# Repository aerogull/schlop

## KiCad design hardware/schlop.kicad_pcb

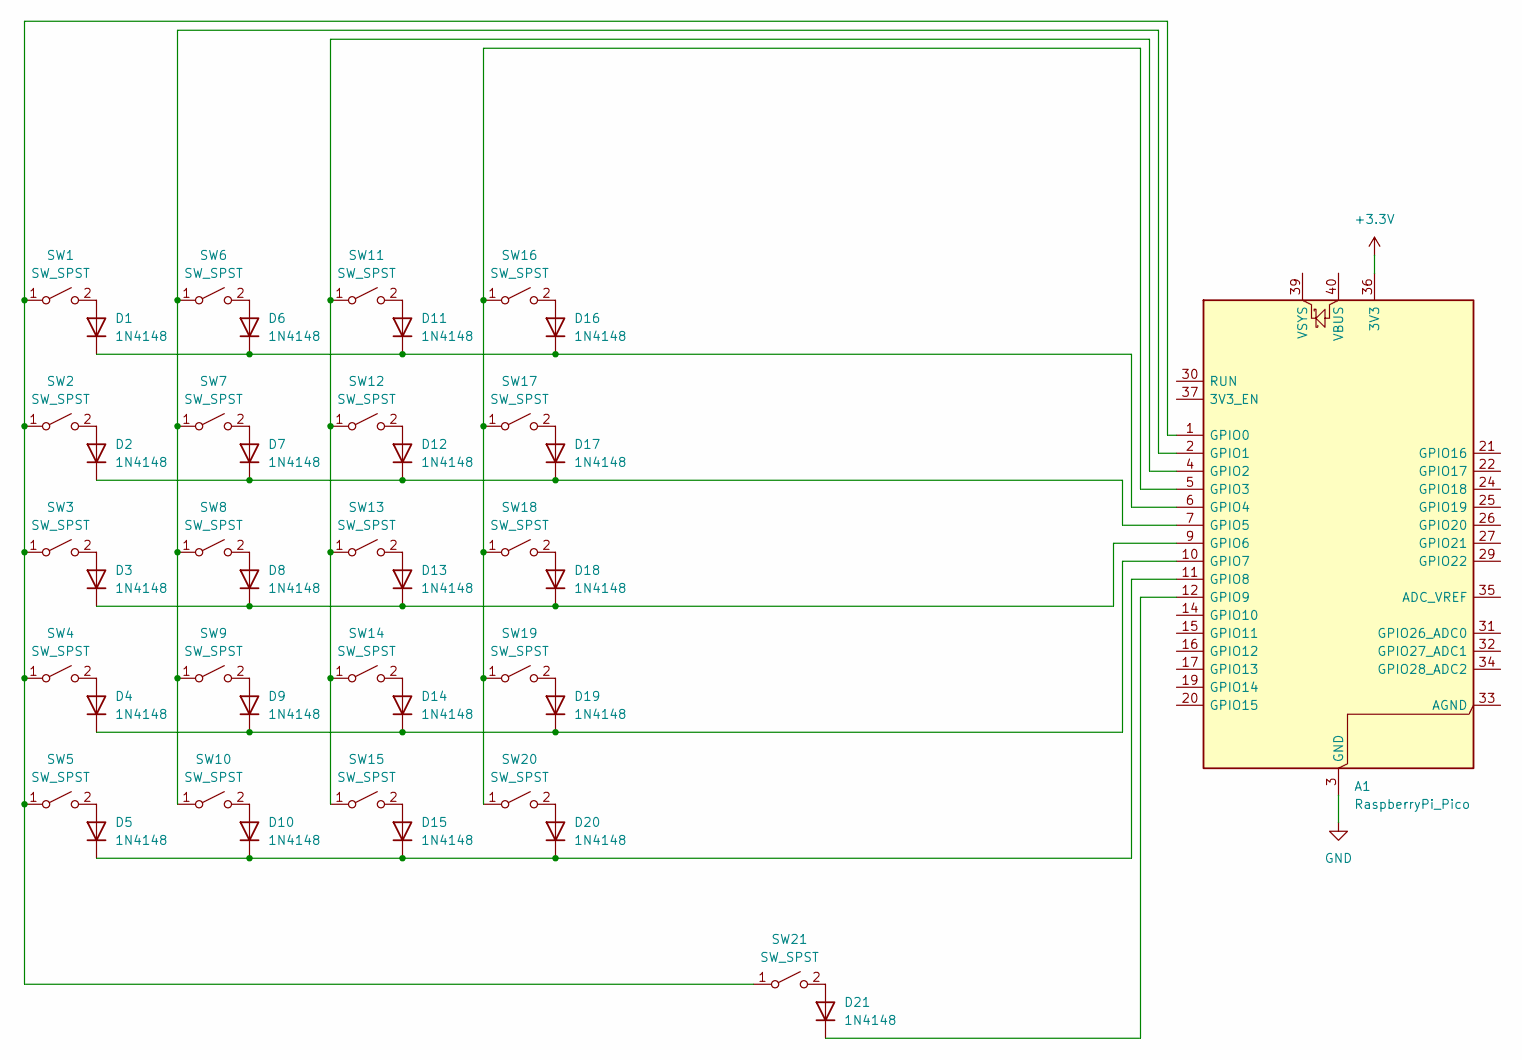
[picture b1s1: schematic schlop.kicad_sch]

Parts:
A1: RaspberryPi_Pico; RaspberryPi_Pico_Common_Unspecified
D1, D2, D3, D4, D5, D6, D7, D8, D9, D10, D11, D12, D13, D14, D15, D16, D17, D18, D19, D20, D21: 1N4148; D_DO-35_SOD27_P7.62mm_Horizontal
SW1, SW2, SW3, SW4, SW5, SW6, SW7, SW8, SW9, SW10, SW11, SW12, SW13, SW14, SW15, SW16, SW17, SW18, SW19, SW20: SW_SPST; MX-Hotswap-1U
SW21: SW_SPST; MX-Hotswap-1.75U

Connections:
+3.3V: A1.36 (3V3)
GND: A1.3 (GND), A1.8 (GND), A1.13 (GND), A1.18 (GND), A1.23 (GND), A1.28 (GND), A1.38 (GND)
unnamed: A1.1 (GPIO0), SW1.1 (A), SW2.1 (A), SW3.1 (A), SW4.1 (A), SW5.1 (A), SW21.1 (A)
unnamed: A1.2 (GPIO1), SW6.1 (A), SW7.1 (A), SW8.1 (A), SW9.1 (A), SW10.1 (A)
unnamed: A1.4 (GPIO2), SW11.1 (A), SW12.1 (A), SW13.1 (A), SW14.1 (A), SW15.1 (A)
unnamed: A1.5 (GPIO3), SW16.1 (A), SW17.1 (A), SW18.1 (A), SW19.1 (A), SW20.1 (A)
unnamed: A1.6 (GPIO4), D1.1 (K), D6.1 (K), D11.1 (K), D16.1 (K)
unnamed: A1.7 (GPIO5), D2.1 (K), D7.1 (K), D12.1 (K), D17.1 (K)
unnamed: A1.9 (GPIO6), D3.1 (K), D8.1 (K), D13.1 (K), D18.1 (K)
unnamed: A1.10 (GPIO7), D4.1 (K), D9.1 (K), D14.1 (K), D19.1 (K)
unnamed: A1.11 (GPIO8), D5.1 (K), D10.1 (K), D15.1 (K), D20.1 (K)
unnamed: A1.12 (GPIO9), D21.1 (K)
unnamed: D1.2 (A), SW1.2 (B)
unnamed: D2.2 (A), SW2.2 (B)
unnamed: D3.2 (A), SW3.2 (B)
unnamed: D4.2 (A), SW4.2 (B)
unnamed: D5.2 (A), SW5.2 (B)
unnamed: D6.2 (A), SW6.2 (B)
unnamed: D7.2 (A), SW7.2 (B)
unnamed: D8.2 (A), SW8.2 (B)
unnamed: D9.2 (A), SW9.2 (B)
unnamed: D10.2 (A), SW10.2 (B)
unnamed: D11.2 (A), SW11.2 (B)
unnamed: D12.2 (A), SW12.2 (B)
unnamed: D13.2 (A), SW13.2 (B)
unnamed: D14.2 (A), SW14.2 (B)
unnamed: D15.2 (A), SW15.2 (B)
unnamed: D16.2 (A), SW16.2 (B)
unnamed: D17.2 (A), SW17.2 (B)
unnamed: D18.2 (A), SW18.2 (B)
unnamed: D19.2 (A), SW19.2 (B)
unnamed: D20.2 (A), SW20.2 (B)
unnamed: D21.2 (A), SW21.2 (B)

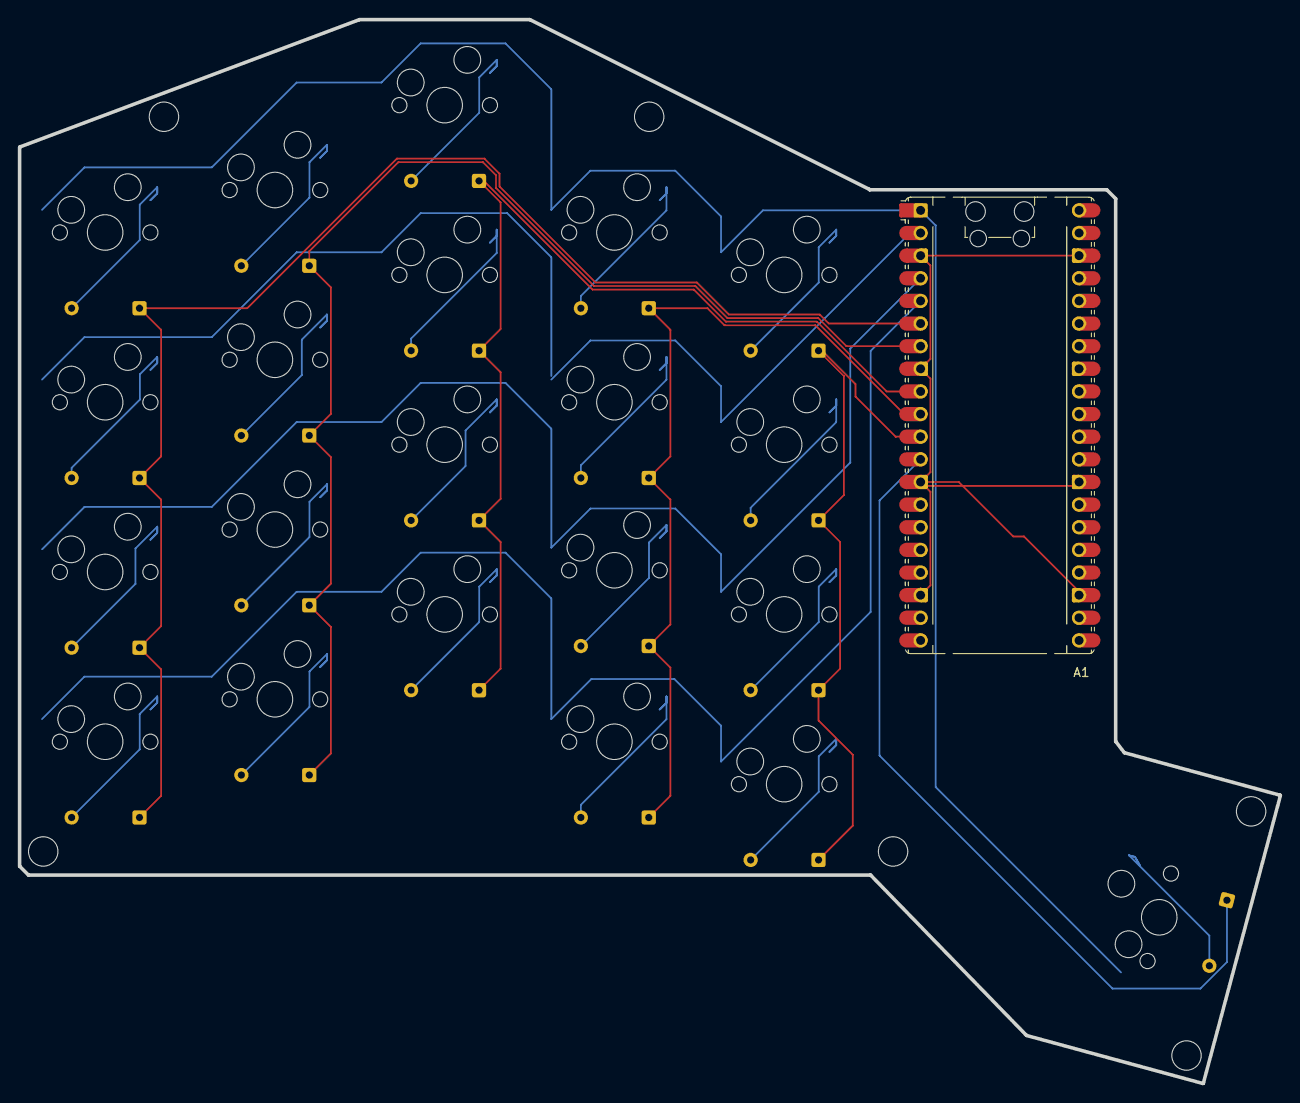
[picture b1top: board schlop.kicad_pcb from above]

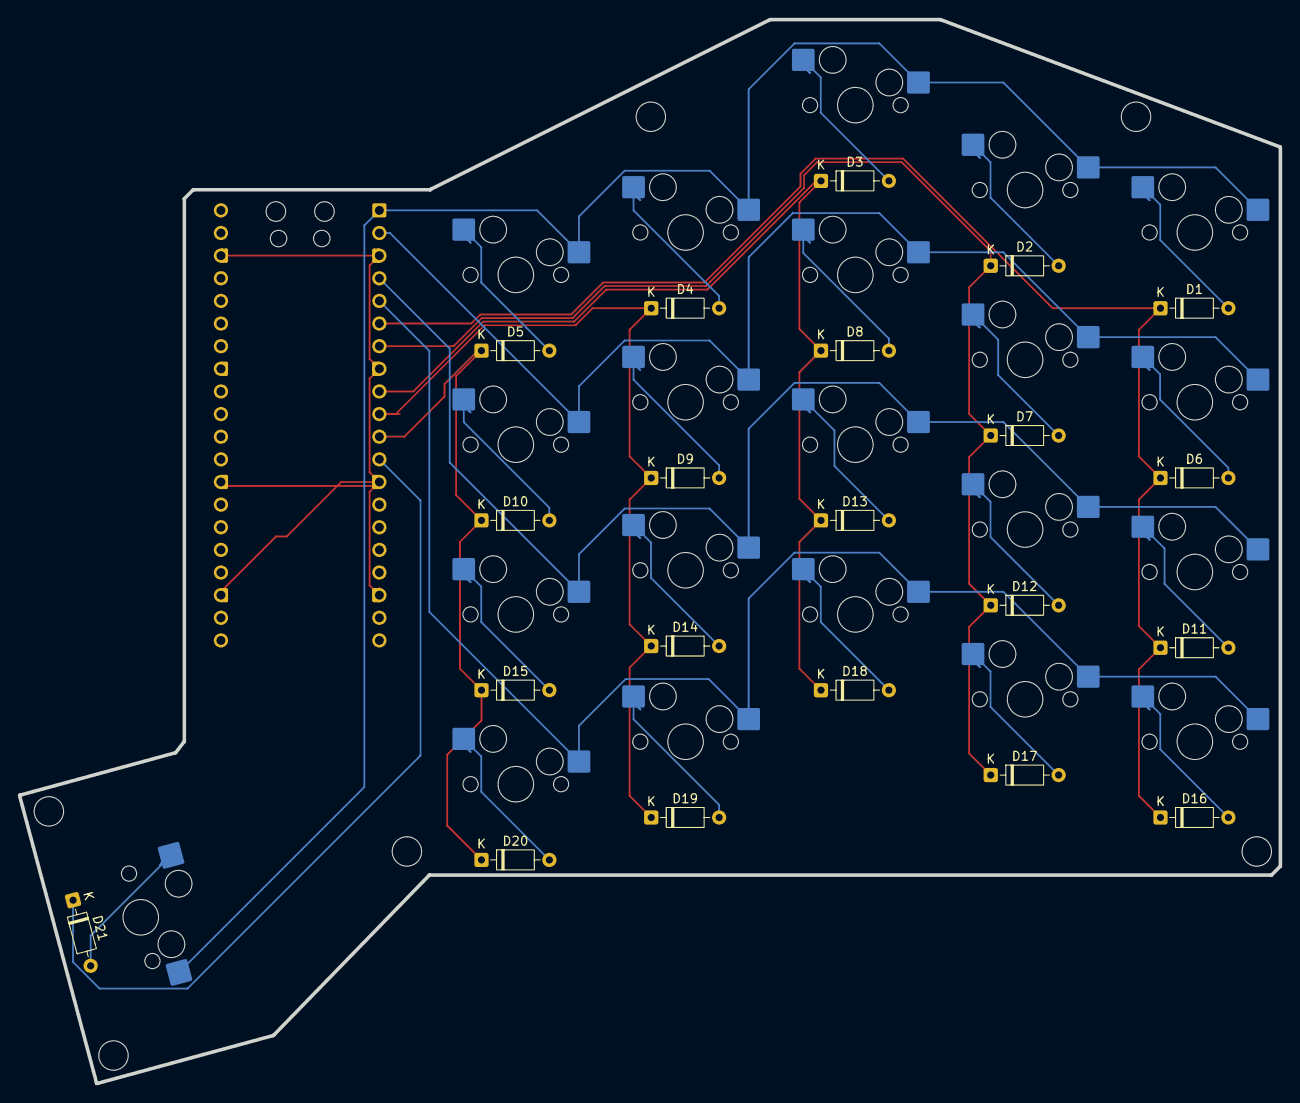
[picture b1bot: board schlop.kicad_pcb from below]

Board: 2 copper layers, 141.5 x 119.4 mm, 43 parts (21 on the bottom side), 32 nets.

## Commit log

2026-05-24 mostly finished hardware
2026-05-26 more pcb changes
2026-05-29 finished pcb routing and mounting
2026-06-10 bottom case mostly finished
